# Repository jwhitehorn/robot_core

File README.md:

## Overview

Open design for a programable real-time robotics controller.

See [Byte Code](https://github.com/jwhitehorn/robot_core/wiki/Byte-Code).

## Status

This project is in a pre-alpha state, or in other words; Robot Core is currently a rough prototype. 
With that said, it's design, function, and features will change drastically as it evolves.

## Hardware & Documentation License

Copyright (c) 2013, [Jason Whitehorn](https://github.com/jwhitehorn) released under the terms of:

[Creative Commons CC-BY-SA 3.0](http://creativecommons.org/licenses/by-sa/3.0/us/)

## Software License

Copyright (c) 2013, [Jason Whitehorn](https://github.com/jwhitehorn) 
All rights reserved.

Redistribution and use in source and binary forms, with or without modification, are permitted provided that the following conditions are met:

* Redistributions of source code must retain the above copyright notice, this list of conditions and the following disclaimer.
* Redistributions in binary form must reproduce the above copyright notice, this list of conditions and the following disclaimer in the documentation and/or other materials provided with the distribution.

THIS SOFTWARE IS PROVIDED BY THE COPYRIGHT HOLDERS AND CONTRIBUTORS "AS IS" AND ANY EXPRESS OR IMPLIED WARRANTIES, INCLUDING, BUT NOT LIMITED TO, THE IMPLIED WARRANTIES OF MERCHANTABILITY AND FITNESS FOR A PARTICULAR PURPOSE ARE DISCLAIMED. IN NO EVENT SHALL THE COPYRIGHT HOLDER OR CONTRIBUTORS BE LIABLE FOR ANY DIRECT, INDIRECT, INCIDENTAL, SPECIAL, EXEMPLARY, OR CONSEQUENTIAL DAMAGES (INCLUDING, BUT NOT LIMITED TO, PROCUREMENT OF SUBSTITUTE GOODS OR SERVICES; LOSS OF USE, DATA, OR PROFITS; OR BUSINESS INTERRUPTION) HOWEVER CAUSED AND ON ANY THEORY OF LIABILITY, WHETHER IN CONTRACT, STRICT LIABILITY, OR TORT (INCLUDING NEGLIGENCE OR OTHERWISE) ARISING IN ANY WAY OUT OF THE USE OF THIS SOFTWARE, EVEN IF ADVISED OF THE POSSIBILITY OF SUCH DAMAGE.

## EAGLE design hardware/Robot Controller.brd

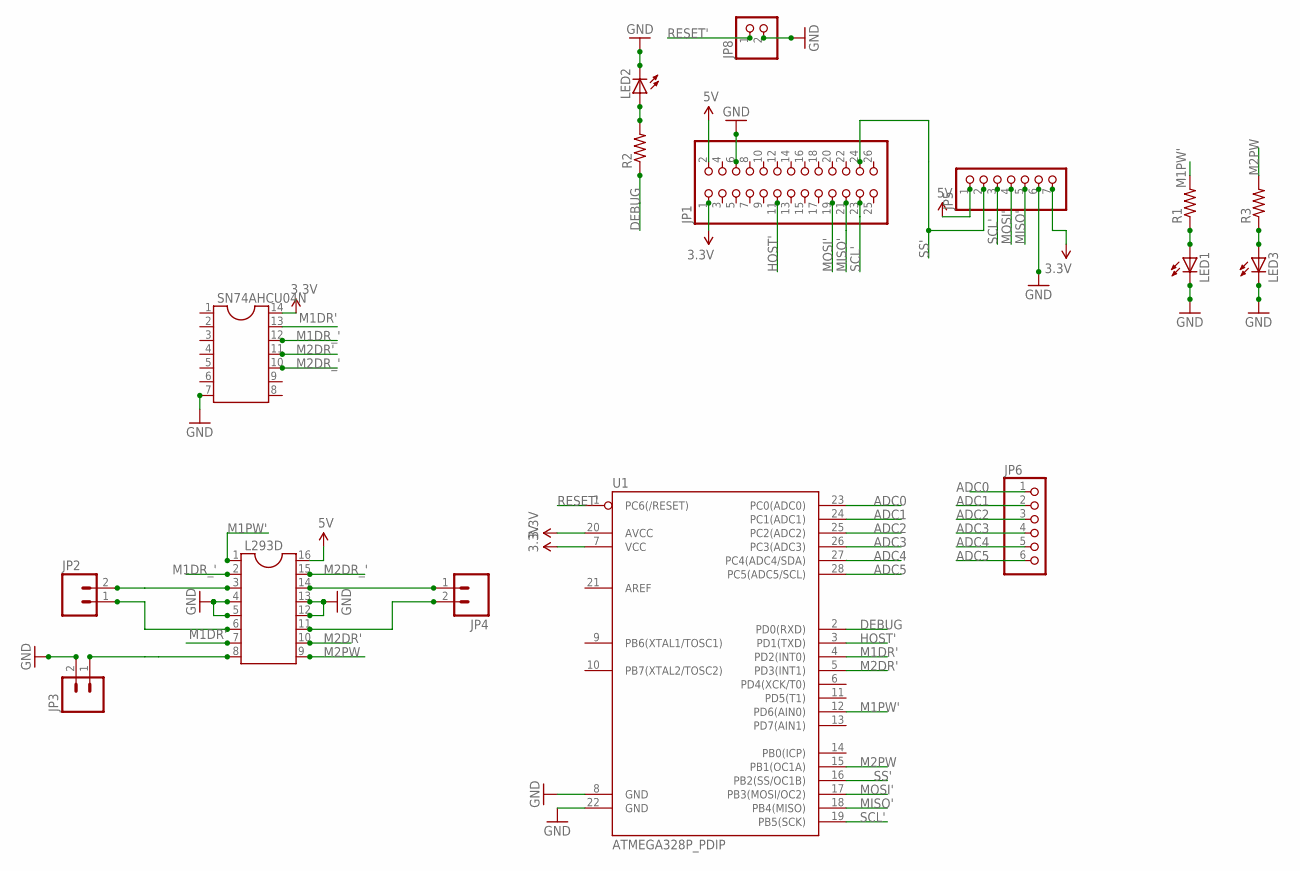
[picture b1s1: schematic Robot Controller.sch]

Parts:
JP1: PINHD-2X13; 2X13
JP2, JP3, JP4: M025MM; SCREWTERMINAL-5MM-2
JP5: PINHD-1X7; 1X07
JP6: PINHD-1X6; 1X06
JP8: PINHD-1X2; 1X02
L293D: DIL16S; SOCKET-16
LED1, LED2, LED3: LEDSMT1206; 1206
R1, R2, R3: R-US_R3216; R3216
SN74AHCU04N: DIL14S; SOCKET-14
U1: ATMEGA328P_PDIP; DIL28-3

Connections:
3.3V: JP1.1, JP5.7, SN74AHCU04N.14, U1.7 (VCC), U1.20 (AVCC)
5V: JP1.2, JP5.1, L293D.16
ADC0: JP6.1, U1.23 (PC0(ADC0))
ADC1: JP6.2, U1.24 (PC1(ADC1))
ADC2: JP6.3, U1.25 (PC2(ADC2))
ADC3: JP6.4, U1.26 (PC3(ADC3))
ADC4: JP6.5, U1.27 (PC4(ADC4/SDA))
ADC5: JP6.6, U1.28 (PC5(ADC5/SCL))
DEBUG: R2.1, U1.2 (PD0(RXD))
GND: JP1.6, JP3.2, JP5.6, JP8.2, L293D.4, L293D.5, L293D.12, L293D.13, LED1.C, LED2.C, LED3.C, SN74AHCU04N.7, U1.8 (GND), U1.22 (GND)
HOST': JP1.11, U1.3 (PD1(TXD))
M1DR': L293D.7, SN74AHCU04N.13, U1.4 (PD2(INT0))
M1DR_': L293D.2, SN74AHCU04N.12
M1PW': L293D.1, R1.2, U1.12 (PD6(AIN0))
M2DR': L293D.10, SN74AHCU04N.11, U1.5 (PD3(INT1))
M2DR_': L293D.15, SN74AHCU04N.10
M2PW: L293D.9, R3.2, U1.15 (PB1(OC1A))
MISO': JP1.21, JP5.5, U1.18 (PB4(MISO))
MOSI': JP1.19, JP5.4, U1.17 (PB3(MOSI/OC2))
unnamed: LED1.A, R1.1
unnamed: JP2.2, L293D.3
unnamed: JP2.1, L293D.6
unnamed: JP3.1, L293D.8
unnamed: LED3.A, R3.1
unnamed: LED2.A, R2.2
unnamed: JP4.1, L293D.14
unnamed: JP4.2, L293D.11
RESET': JP8.1, U1.1 (PC6(/RESET))
SCL': JP1.23, JP5.3, U1.19 (PB5(SCK))
SS': JP1.24, JP5.2, U1.16 (PB2(SS/OC1B))

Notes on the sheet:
SCL'
MISO'
MOSI'
RESET'
M1PW'
M2PW
M1DR'
M2DR'
M1DR_'
M2DR_'
DEBUG
HOST'
SS'
ADC0
ADC1
ADC2
ADC3
ADC4
ADC5

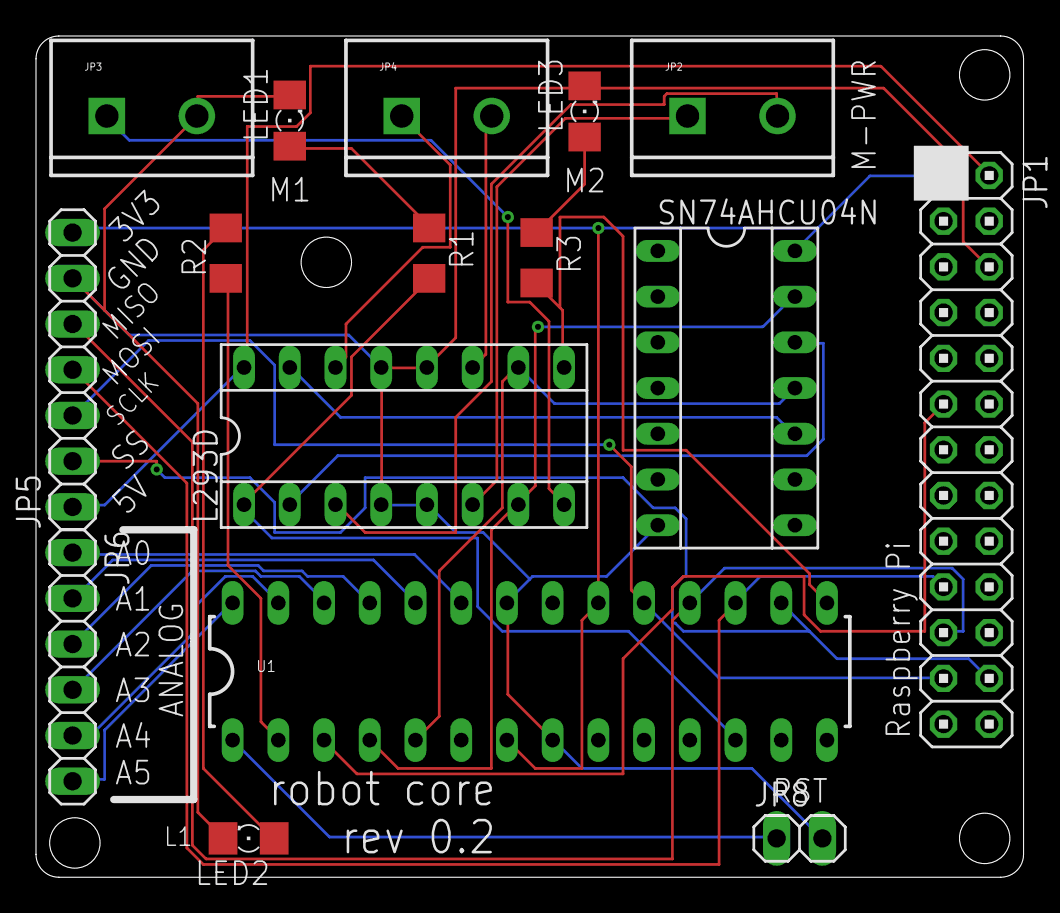
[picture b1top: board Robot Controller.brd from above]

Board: 2 copper layers, 54.9 x 46.7 mm, 16 parts (0 on the bottom side), 30 nets.

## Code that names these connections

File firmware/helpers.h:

//Helper file to abstract away platform specifics.

//Suport for both attiny and atmega devices
#ifdef PORTA
#define ATTINY
#define SPI_VECTOR USI_OVERFLOW_vect
#else
#define ATMEGA
#define SPI_VECTOR SPI_STC_vect
#define USIDR SPDR
#define USISR SPDR
#endif

//ATtiny doesn't support SPI per se, but it can use USI as SPI... let's abstract that...
int spiReceived(){
  #ifdef ATTINY
  int byte = USIDR / 2;
  USISR = (1<<USIOIF);
  USIDR = byte;
  return byte;
  #else
  SPDR = 0x00;  
  return SPDR; 
  #endif
}

void setupSpi(){
  #ifdef ATTINY
  USICR = _BV(USIOIE) | _BV(USIWM0) | _BV(USICS0) | _BV(USICS1);
  USISR = (1<<USIOIF);
  #else
  setup_spi(SPI_MODE_1, SPI_MSB, SPI_INTERRUPT, SPI_SLAVE);
  #endif
}


//General helpers:
#define __output_low(port,pin, portdir, hwpin) port &= ~(1<<pin)    
#define __output_high(port,pin, portdir, hwpin) port |= (1<<pin)
#define __set_input(port, pin, portdir, hwpin) portdir &= ~(1<<pin)
#define __set_output(port, pin, portdir, hwpin) portdir |= (1<<pin)
#define __read_pin(port, pin, portdir, hwpin) hwpin & (1<<pin)

#define outputLow(pin) __output_low(pin)
#define outputHigh(pin) __output_high(pin)
#define setInput(pin) __set_input(pin)
#define setOutput(pin) __set_output(pin)
#define readPin(pin) __read_pin(pin)

#define sleep _delay_ms

//Pins:
#define HOST_PIN    PORTD, PD1, DDRD, PINA
#define DEBUG_PIN   PORTD, PD0, DDRD, PINA
#define M1DR_PIN    PORTD, PD2, DDRD, PIND
#define M2DR_PIN    PORTD, PD3, DDRD, PIND
#define M1PW_PIN    PORTD, PD6, DDRD, PIND
#define M2PW_PIN    PORTB, PB1, DDRB, PINB
#define ADC1_PIN    PORTC, PC1, DDRC, PINC
#define GPIO1_PIN   PORTD, PD7, DDRD, PIND

uint16_t ReadADC(uint8_t ADCchannel){
  //select ADC channel with safety mask
  ADMUX = (ADMUX & 0xF0) | (ADCchannel & 0x0F);
  //single conversion mode
  ADCSRA |= (1<<ADSC);
  // wait until ADC conversion is complete
  while( ADCSRA & (1<<ADSC) );
  return ADC;
}

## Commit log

2013-01-29 added firmware
2013-01-29 added license
2013-01-29 added ignore file
2013-01-29 test script
2013-01-29 added hardware
2013-01-29 swag at byte code
2013-01-29 clean up
2013-01-29 added a host pin
2013-01-30 cleanup & tweaks
2013-01-30 get firmware compiling againf
2013-01-30 switch to using interrupts... a little better luck getting the firmware to take commands
2013-01-30 thinking out how motor direction will be controlled
2013-01-30 update test.rb to us the new bytecode, and also set the clock low for now
2013-01-30 dont multiply by two
2013-01-30 tweak hardware design
2013-01-30 abstract the debug pin
2013-01-30 fixed host pin stupidity
2013-01-31 go from high to low
2013-01-31 perform blink at the end of main
2013-01-31 change host pin
2013-01-31 setup timer 1
2013-01-31 implement motor 2
2013-01-31 got motor 2 working!!!
2013-01-31 update hardware for second motor
2013-01-31 ideas around master/slave robot cores
2013-02-01 WIP dev board
2013-02-01 silkscreen work
2013-02-01 routing
2013-02-01 notes on where to go with firmware
2013-02-02 tighten up PCB
2013-02-02 motor direction control
2013-02-03 syntax error
2013-02-03 formatting
2013-02-04 attempt at RIFEQ implementation
2013-02-05 temp fix to crazy bug
2013-02-05 fixed previous bug by explicitly initializing the command buffer to 0
2013-02-05 working on cleaning up schematic
2013-02-06 need ADC, upgrading to ATmega328
2013-02-06 rough routing
2013-02-06 Rakefile FTW!
2013-02-06 improve Rakefile
2013-02-06 WIP at atmega support
2013-02-06 added Gemfile
2013-02-07 include SPI helper
2013-02-07 got it compiling again, but still borked
2013-02-10 fixed helpers to make them less broken
2013-02-10 significant amount of less-broken
2013-02-10 SPI slave work on the mega
2013-02-10 mega is accepting commands
2013-02-11 abstract away M1PW
2013-02-11 WIP ATmega328 hardware
2013-02-11 update connections to match todays progress
2013-02-12 expose M2PW
2013-02-13 WIP adc
2013-02-14 more WIP adc
2013-02-14 WIP hardware
2013-02-15 fix outline
2013-02-16 change name to be on tPlace, not tStop :-(
2013-02-16 extract the processCommandBuffer function into some more general
2013-02-16 process the table during the runtime loop
2013-02-16 more work on rev0.2 hardware
2013-02-17 thinking out store v. execute of varius commands
2013-02-17 WIP RIFEQ implementation
2013-02-17 work on GPIO pins
2013-02-18 WIP RIFEQ support
2013-02-19 implement RIFLT
2013-02-20 remove dead code
2013-02-21 clean up RIFEQ, RIFLT, and RIFGT
2013-02-22 first steps to a gem
2013-02-23 thoughts on core of gem...
2013-02-23 add class for byte code
2013-02-23 added class for registers
2013-02-24 not sure where this class is headed...
2013-02-25 more thoughts on what the firmware class should do

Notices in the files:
parts and their libraries:
SparkFun-Connectors: Licensing: CC v3.0 Share-Alike You are welcome to use this library for commercial purposes.
